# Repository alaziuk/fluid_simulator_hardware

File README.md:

# Fluid Simulator Pendant Hardware

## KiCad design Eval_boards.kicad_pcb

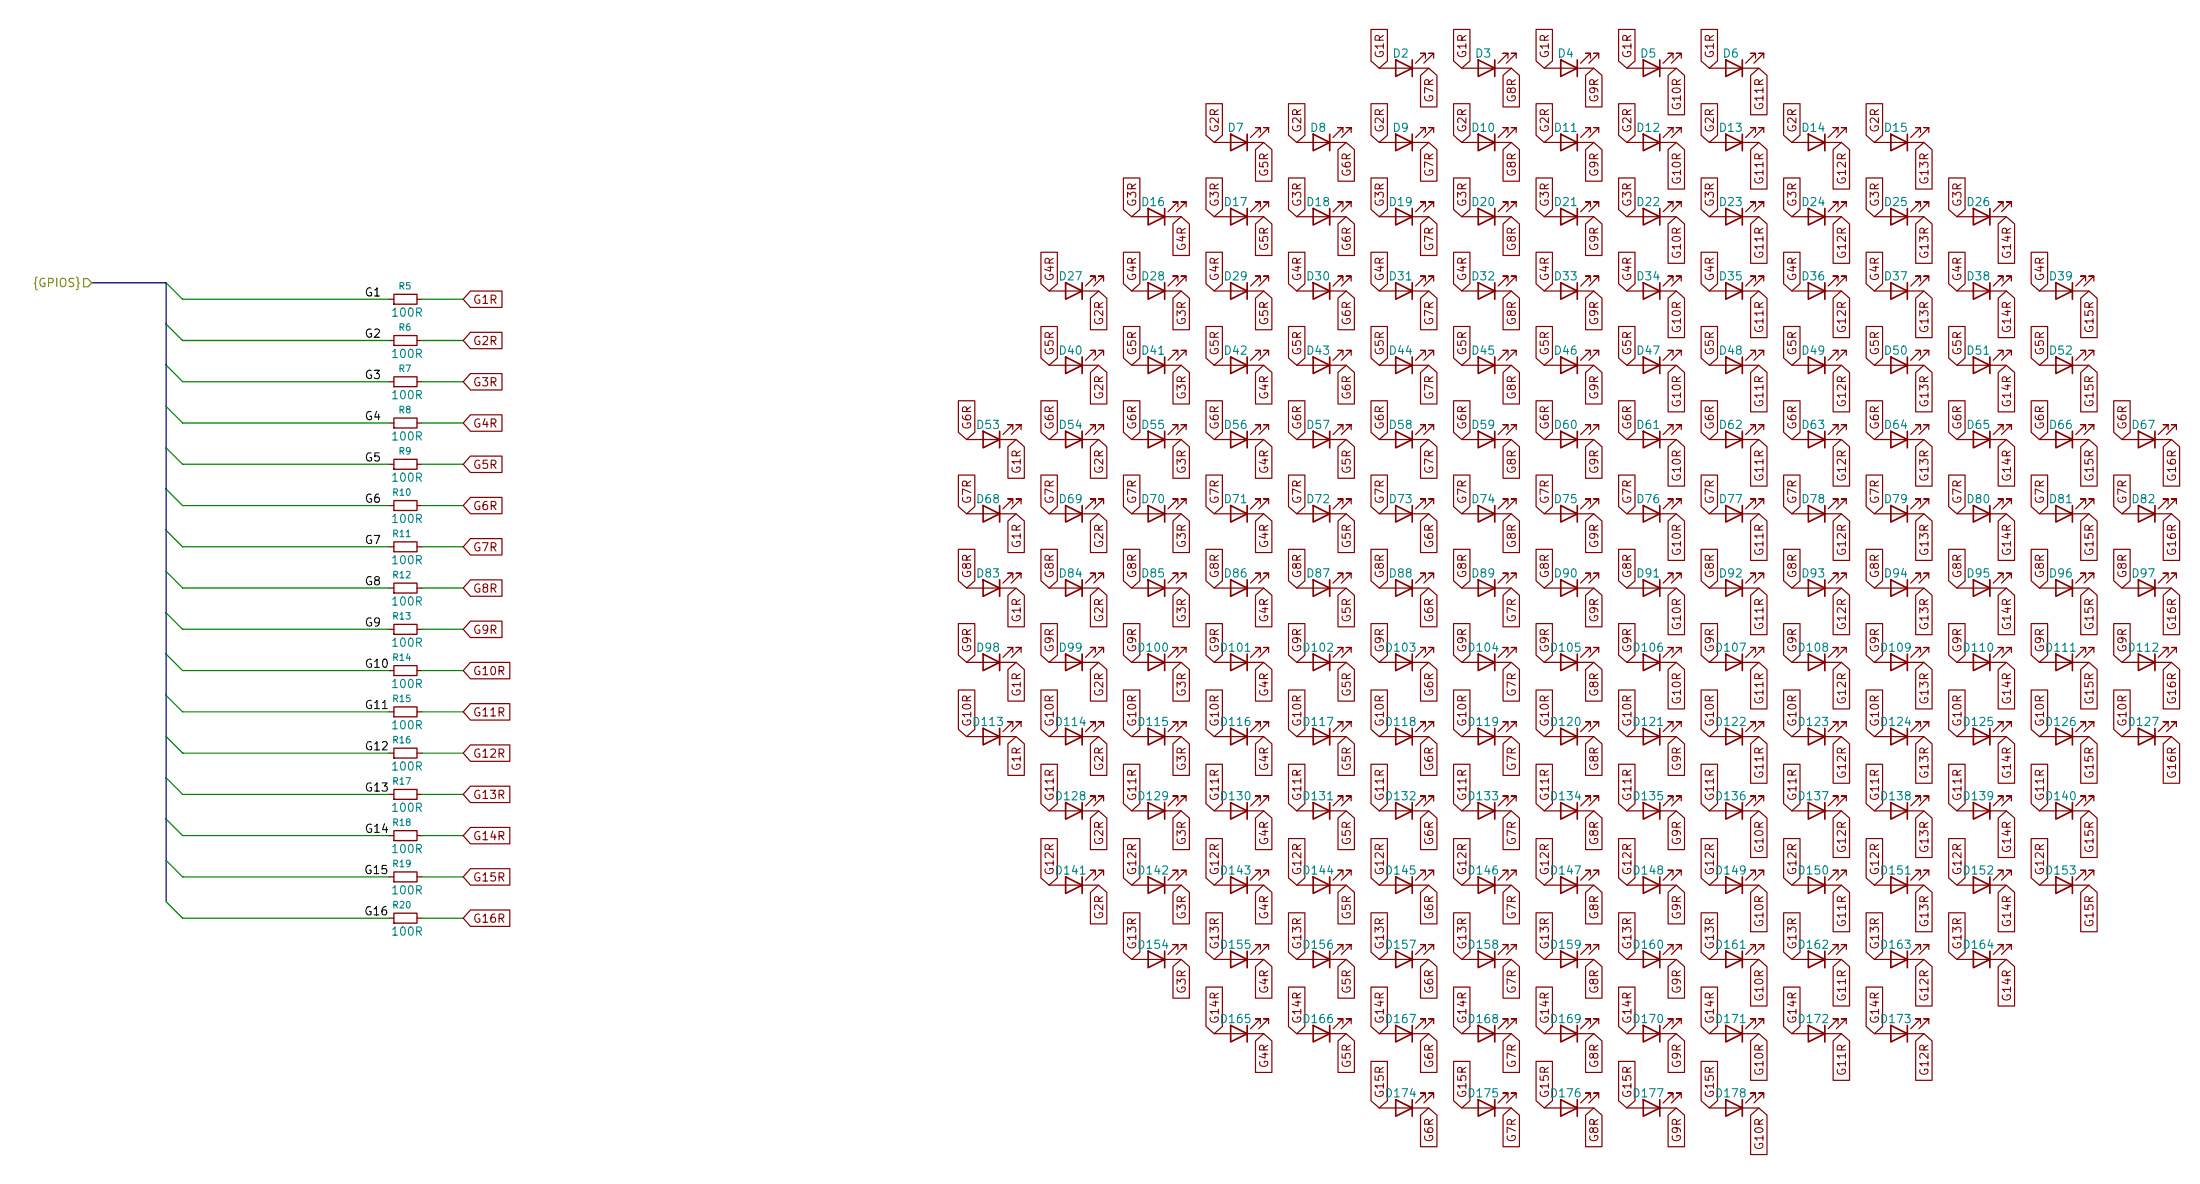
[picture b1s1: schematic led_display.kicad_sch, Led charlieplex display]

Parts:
D2, D3, D4, D5, D6, D7, D8, D9, D10, D11, D12, D13, D14, D15, D16, D17, D18, D19, D20, D21, D22, D23, D24, D25, D26, D27, D28, D29, D30, D31, D32, D33, D34, D35, D36, D37, D38, D39, D40, D41, D42, D43, D44, D45, D46, D47, D48, D49, D50, D51, D52, D53, D54, D55, D56, D57, D58, D59, D60, D61, D62, D63, D64, D65, D66, D67, D68, D69, D70, D71, D72, D73, D74, D75, D76, D77, D78, D79, D80, D81, D82, D83, D84, D85, D86, D87, D88, D89, D90, D91, D92, D93, D94, D95, D96, D97, D98, D99, D100, D101, D102, D103, D104, D105, D106, D107, D108, D109, D110, D111, D112, D113, D114, D115, D116, D117, D118, D119, D120, D121, D122, D123, D124, D125, D126, D127, D128, D129, D130, D131, D132, D133, D134, D135, D136, D137, D138, D139, D140, D141, D142, D143, D144, D145, D146, D147, D148, D149, D150, D151, D152, D153, D154, D155, D156, D157, D158, D159, D160, D161, D162, D163, D164, D165, D166, D167, D168, D169, D170, D171, D172, D173, D174, D175, D176, D177, D178: blue led; D_0603_1608Metric
R5, R6, R7, R8, R9, R10, R11, R12, R13, R14, R15, R16, R17, R18, R19, R20: 100R; R_0603_1608Metric

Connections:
/LED_DISPLAY/G1: R5.1; also elsewhere on the board
/LED_DISPLAY/G2: R6.1; also elsewhere on the board
/LED_DISPLAY/G3: R7.1; also elsewhere on the board
/LED_DISPLAY/G4: R8.1; also elsewhere on the board
/LED_DISPLAY/G5: R9.1; also elsewhere on the board
/LED_DISPLAY/G6: R10.1; also elsewhere on the board
/LED_DISPLAY/G7: R11.1; also elsewhere on the board
/LED_DISPLAY/G8: R12.1; also elsewhere on the board
/LED_DISPLAY/G9: R13.1; also elsewhere on the board
/LED_DISPLAY/G10: R14.1; also elsewhere on the board
/LED_DISPLAY/G11: R15.1; also elsewhere on the board
/LED_DISPLAY/G12: R16.1; also elsewhere on the board
/LED_DISPLAY/G13: R17.1; also elsewhere on the board
/LED_DISPLAY/G14: R18.1; also elsewhere on the board
/LED_DISPLAY/G15: R19.1; also elsewhere on the board
/LED_DISPLAY/G16: R20.1; also elsewhere on the board
G1R: D2.2 (A), D3.2 (A), D4.2 (A), D5.2 (A), D6.2 (A), D53.1 (K), D68.1 (K), D83.1 (K), D98.1 (K), D113.1 (K), R5.2
G2R: D7.2 (A), D8.2 (A), D9.2 (A), D10.2 (A), D11.2 (A), D12.2 (A), D13.2 (A), D14.2 (A), D15.2 (A), D27.1 (K), D40.1 (K), D54.1 (K), D69.1 (K), D84.1 (K), D99.1 (K), D114.1 (K), D128.1 (K), D141.1 (K), R6.2
G3R: D16.2 (A), D17.2 (A), D18.2 (A), D19.2 (A), D20.2 (A), D21.2 (A), D22.2 (A), D23.2 (A), D24.2 (A), D25.2 (A), D26.2 (A), D28.1 (K), D41.1 (K), D55.1 (K), D70.1 (K), D85.1 (K), D100.1 (K), D115.1 (K), D129.1 (K), D142.1 (K), D154.1 (K), R7.2
G4R: D16.1 (K), D27.2 (A), D28.2 (A), D29.2 (A), D30.2 (A), D31.2 (A), D32.2 (A), D33.2 (A), D34.2 (A), D35.2 (A), D36.2 (A), D37.2 (A), D38.2 (A), D39.2 (A), D42.1 (K), D56.1 (K), D71.1 (K), D86.1 (K), D101.1 (K), D116.1 (K), D130.1 (K), D143.1 (K), D155.1 (K), D165.1 (K), R8.2
G5R: D7.1 (K), D17.1 (K), D29.1 (K), D40.2 (A), D41.2 (A), D42.2 (A), D43.2 (A), D44.2 (A), D45.2 (A), D46.2 (A), D47.2 (A), D48.2 (A), D49.2 (A), D50.2 (A), D51.2 (A), D52.2 (A), D57.1 (K), D72.1 (K), D87.1 (K), D102.1 (K), D117.1 (K), D131.1 (K), D144.1 (K), D156.1 (K), D166.1 (K), R9.2
G6R: D8.1 (K), D18.1 (K), D30.1 (K), D43.1 (K), D53.2 (A), D54.2 (A), D55.2 (A), D56.2 (A), D57.2 (A), D58.2 (A), D59.2 (A), D60.2 (A), D61.2 (A), D62.2 (A), D63.2 (A), D64.2 (A), D65.2 (A), D66.2 (A), D67.2 (A), D73.1 (K), D88.1 (K), D103.1 (K), D118.1 (K), D132.1 (K), D145.1 (K), D157.1 (K), D167.1 (K), D174.1 (K), R10.2
G7R: D2.1 (K), D9.1 (K), D19.1 (K), D31.1 (K), D44.1 (K), D58.1 (K), D68.2 (A), D69.2 (A), D70.2 (A), D71.2 (A), D72.2 (A), D73.2 (A), D74.2 (A), D75.2 (A), D76.2 (A), D77.2 (A), D78.2 (A), D79.2 (A), D80.2 (A), D81.2 (A), D82.2 (A), D89.1 (K), D104.1 (K), D119.1 (K), D133.1 (K), D146.1 (K), D158.1 (K), D168.1 (K), D175.1 (K), R11.2
G8R: D3.1 (K), D10.1 (K), D20.1 (K), D32.1 (K), D45.1 (K), D59.1 (K), D74.1 (K), D83.2 (A), D84.2 (A), D85.2 (A), D86.2 (A), D87.2 (A), D88.2 (A), D89.2 (A), D90.2 (A), D91.2 (A), D92.2 (A), D93.2 (A), D94.2 (A), D95.2 (A), D96.2 (A), D97.2 (A), D105.1 (K), D120.1 (K), D134.1 (K), D147.1 (K), D159.1 (K), D169.1 (K), D176.1 (K), R12.2
G9R: D4.1 (K), D11.1 (K), D21.1 (K), D33.1 (K), D46.1 (K), D60.1 (K), D75.1 (K), D90.1 (K), D98.2 (A), D99.2 (A), D100.2 (A), D101.2 (A), D102.2 (A), D103.2 (A), D104.2 (A), D105.2 (A), D106.2 (A), D107.2 (A), D108.2 (A), D109.2 (A), D110.2 (A), D111.2 (A), D112.2 (A), D121.1 (K), D135.1 (K), D148.1 (K), D160.1 (K), D170.1 (K), D177.1 (K), R13.2
G10R: D5.1 (K), D12.1 (K), D22.1 (K), D34.1 (K), D47.1 (K), D61.1 (K), D76.1 (K), D91.1 (K), D106.1 (K), D113.2 (A), D114.2 (A), D115.2 (A), D116.2 (A), D117.2 (A), D118.2 (A), D119.2 (A), D120.2 (A), D121.2 (A), D122.2 (A), D123.2 (A), D124.2 (A), D125.2 (A), D126.2 (A), D127.2 (A), D136.1 (K), D149.1 (K), D161.1 (K), D171.1 (K), D178.1 (K), R14.2
G11R: D6.1 (K), D13.1 (K), D23.1 (K), D35.1 (K), D48.1 (K), D62.1 (K), D77.1 (K), D92.1 (K), D107.1 (K), D122.1 (K), D128.2 (A), D129.2 (A), D130.2 (A), D131.2 (A), D132.2 (A), D133.2 (A), D134.2 (A), D135.2 (A), D136.2 (A), D137.2 (A), D138.2 (A), D139.2 (A), D140.2 (A), D150.1 (K), D162.1 (K), D172.1 (K), R15.2
G12R: D14.1 (K), D24.1 (K), D36.1 (K), D49.1 (K), D63.1 (K), D78.1 (K), D93.1 (K), D108.1 (K), D123.1 (K), D137.1 (K), D141.2 (A), D142.2 (A), D143.2 (A), D144.2 (A), D145.2 (A), D146.2 (A), D147.2 (A), D148.2 (A), D149.2 (A), D150.2 (A), D151.2 (A), D152.2 (A), D153.2 (A), D163.1 (K), D173.1 (K), R16.2
G13R: D15.1 (K), D25.1 (K), D37.1 (K), D50.1 (K), D64.1 (K), D79.1 (K), D94.1 (K), D109.1 (K), D124.1 (K), D138.1 (K), D151.1 (K), D154.2 (A), D155.2 (A), D156.2 (A), D157.2 (A), D158.2 (A), D159.2 (A), D160.2 (A), D161.2 (A), D162.2 (A), D163.2 (A), D164.2 (A), R17.2
G14R: D26.1 (K), D38.1 (K), D51.1 (K), D65.1 (K), D80.1 (K), D95.1 (K), D110.1 (K), D125.1 (K), D139.1 (K), D152.1 (K), D164.1 (K), D165.2 (A), D166.2 (A), D167.2 (A), D168.2 (A), D169.2 (A), D170.2 (A), D171.2 (A), D172.2 (A), D173.2 (A), R18.2
G15R: D39.1 (K), D52.1 (K), D66.1 (K), D81.1 (K), D96.1 (K), D111.1 (K), D126.1 (K), D140.1 (K), D153.1 (K), D174.2 (A), D175.2 (A), D176.2 (A), D177.2 (A), D178.2 (A), R19.2
G16R: D67.1 (K), D82.1 (K), D97.1 (K), D112.1 (K), D127.1 (K), R20.2

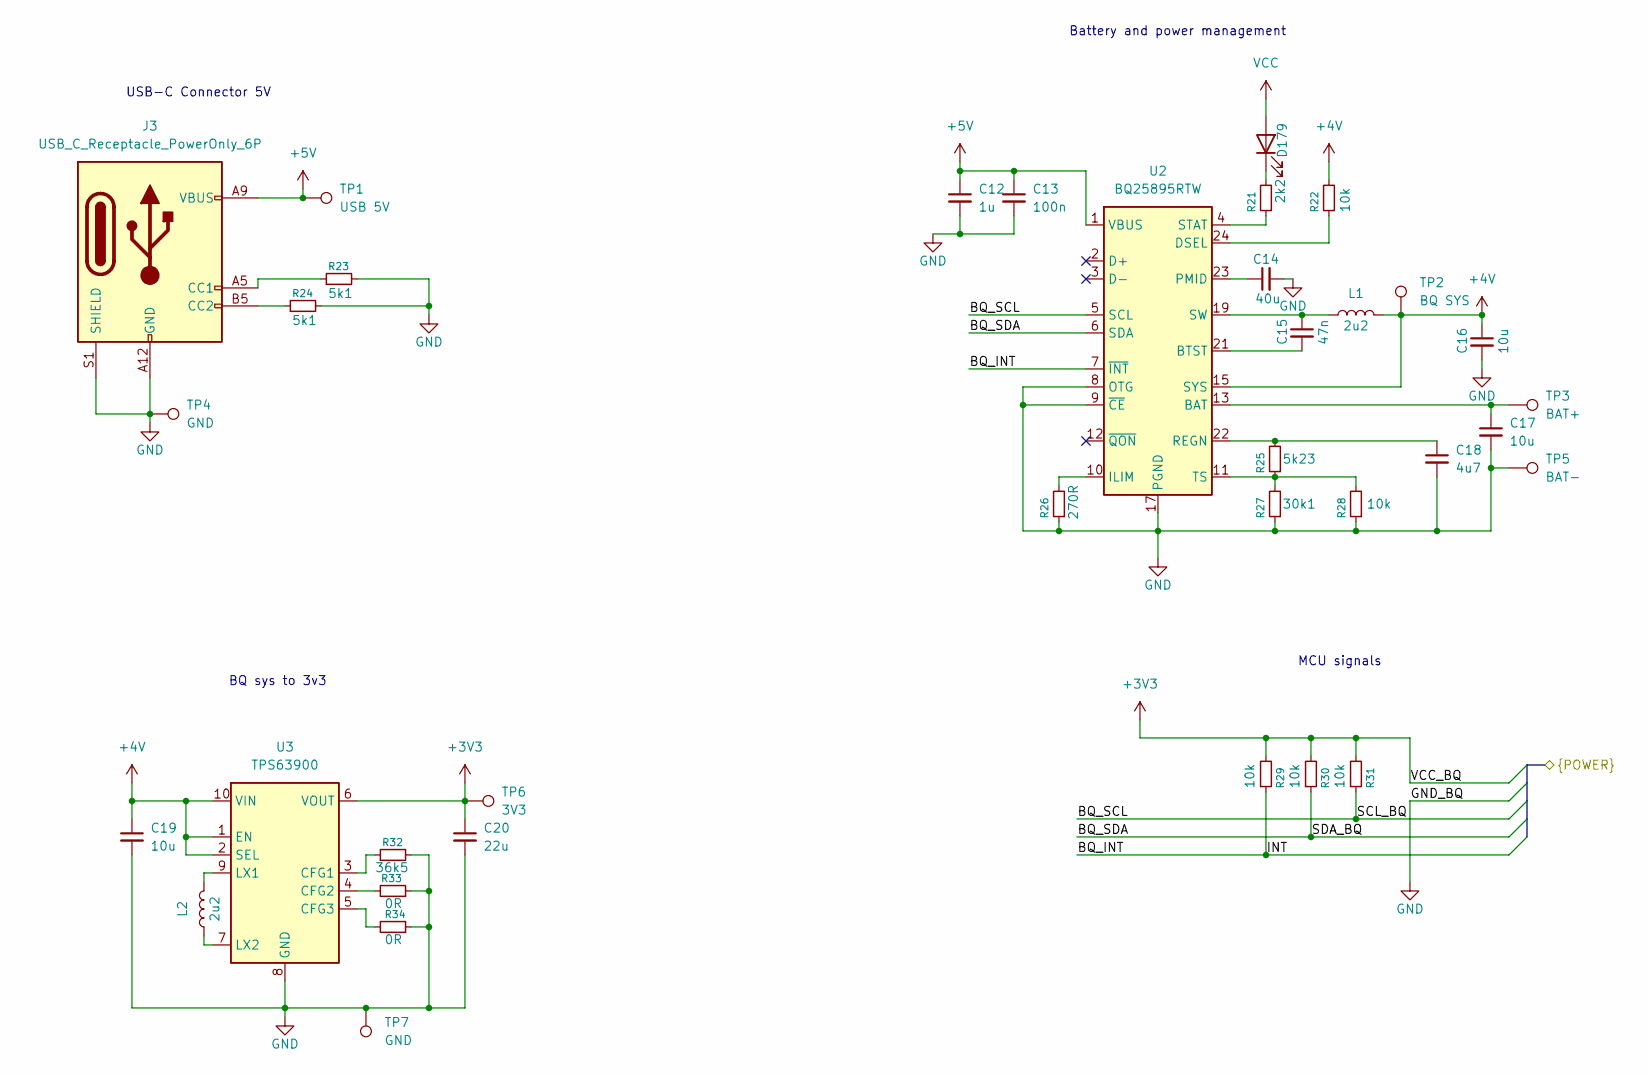
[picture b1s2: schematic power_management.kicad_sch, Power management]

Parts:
C12: 1u; C_0603_1608Metric
C13: 100n; C_0603_1608Metric
C14: 40u; C_0603_1608Metric
C15: 47n; C_0603_1608Metric
C16, C17, C19: 10u; C_0603_1608Metric
C18: 4u7; C_0603_1608Metric
C20: 22u; C_0603_1608Metric
D179: blue led; D_0603_1608Metric
J3: USB_C_Receptacle_PowerOnly_6P; USB_C_Receptacle_GCT_USB4135-GF-A_6P_TopMnt_Horizontal
L1, L2: 2u2; L_0603_1608Metric
R21: 2k2; R_0603_1608Metric
R22, R28, R29, R30, R31: 10k; R_0603_1608Metric
R23, R24: 5k1; R_0603_1608Metric
R25: 5k23; R_0603_1608Metric
R26: 270R; R_0603_1608Metric
R27: 30k1; R_0603_1608Metric
R32: 36k5; R_0603_1608Metric
R33, R34: 0R; R_0603_1608Metric
TP1: USB 5V; TestPoint_Pad_D1.0mm
TP2: BQ SYS; TestPoint_Pad_D1.0mm
TP3: BAT+; TestPoint_Pad_D2.5mm
TP4, TP7: GND; TestPoint_Pad_D1.0mm
TP5: BAT-; TestPoint_Pad_D2.5mm
TP6: 3V3; TestPoint_Pad_D1.0mm
U2: BQ25895RTW; Texas_RTW_WQFN-24-1EP_4x4mm_P0.5mm_EP2.7x2.7mm_ThermalVias
U3: TPS63900; WSON-10-1EP_2.5x2.5mm_P0.5mm_EP1.2x2mm_ThermalVias

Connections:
+3V3: C20.1, R29.2, R30.2, R31.2, TP6.1, U3.6 (VOUT); also elsewhere on the board
+4V: C16.1, C19.1, L1.2, R22.2, TP2.1, U2.15 (SYS), U2.16 (SYS), U3.1 (EN), U3.2 (SEL), U3.10 (VIN); also elsewhere on the board
+5V: C12.1, C13.1, J3.A9 (VBUS), J3.B9 (VBUS), TP1.1, U2.1 (VBUS); also elsewhere on the board
/ACCELEROMETER/SCL_A: R31.1, U2.5 (SCL); also elsewhere on the board
/ACCELEROMETER/SDA_A: R30.1, U2.6 (SDA); also elsewhere on the board
/MCU/INT: R29.1, U2.7 (~INT); also elsewhere on the board
GND: C12.2, C13.2, C14.2, C16.2, C17.2, C18.2, C19.2, C20.2, J3.A12 (GND), J3.B12 (GND), J3.S1 (SHIELD), R23.2, R24.2, R26.1, R27.1, R28.1, R32.2, R33.1, R34.1, TP4.1, TP5.1, TP7.1, U2.8 (OTG), U2.9 (~CE), U2.17 (PGND), U2.18 (PGND), U2.25 (PGND), U3.8 (GND), U3.11 (GND); also elsewhere on the board
unnamed: C15.1, L1.1, U2.19 (SW), U2.20 (SW)
unnamed 54: C17.1, TP3.1, U2.13 (BAT), U2.14 (BAT); also elsewhere on the board
unnamed: D179.1 (K), R21.2
unnamed: J3.A5 (CC1), R23.1
unnamed: J3.B5 (CC2), R24.1
unnamed: C15.2, U2.21 (BTST)
unnamed: R22.1, U2.24 (DSEL)
unnamed: R26.2, U2.10 (ILIM)
unnamed: C14.1, U2.23 (PMID)
unnamed: C18.1, R25.2, U2.22 (REGN)
unnamed: R21.1, U2.4 (STAT)
unnamed: R25.1, R27.2, R28.2, U2.11 (TS)
unnamed: R32.1, U3.3 (CFG1)
unnamed: R33.2, U3.4 (CFG2)
unnamed: R34.2, U3.5 (CFG3)
unnamed: L2.1, U3.9 (LX1)
unnamed: L2.2, U3.7 (LX2)
VCC: D179.2 (A)

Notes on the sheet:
BQ sys to 3v3
MCU signals
Battery and power management
USB-C Connector 5V

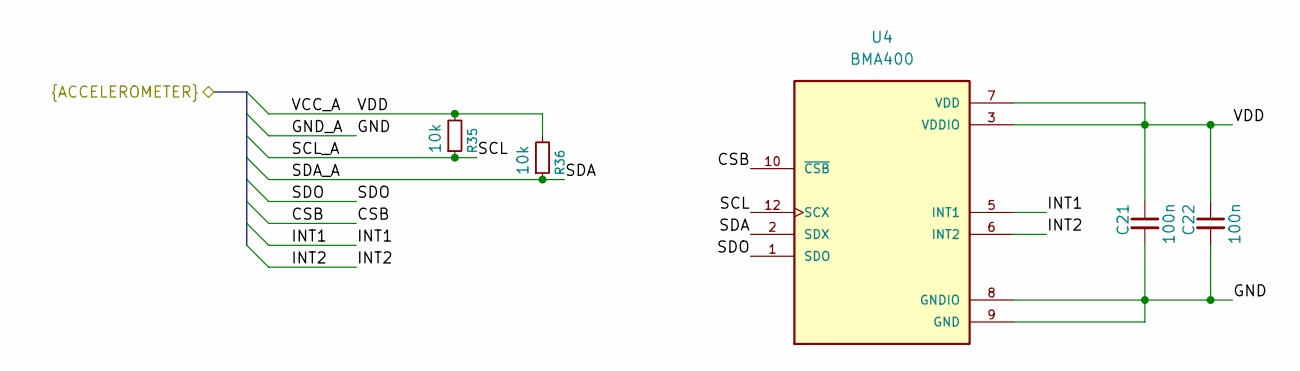
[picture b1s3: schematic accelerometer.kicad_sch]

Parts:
C21, C22: 100n; C_0603_1608Metric
R35, R36: 10k; R_0603_1608Metric
U4: BMA400; XDCR_BMA400

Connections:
+3V3: C21.1, C22.1, R35.2, R36.2, U4.3 (VDDIO), U4.7 (VDD), U4.10 (~CSB); also elsewhere on the board
/ACCELEROMETER/INT1: U4.5 (INT1); also elsewhere on the board
/ACCELEROMETER/INT2: U4.6 (INT2); also elsewhere on the board
/ACCELEROMETER/SCL_A: R35.1, U4.12 (SCX); also elsewhere on the board
/ACCELEROMETER/SDA_A: R36.1, U4.2 (SDX); also elsewhere on the board
/ACCELEROMETER/SDO: U4.1 (SDO); also elsewhere on the board
GND: C21.2, C22.2, U4.8 (GNDIO), U4.9 (GND); also elsewhere on the board

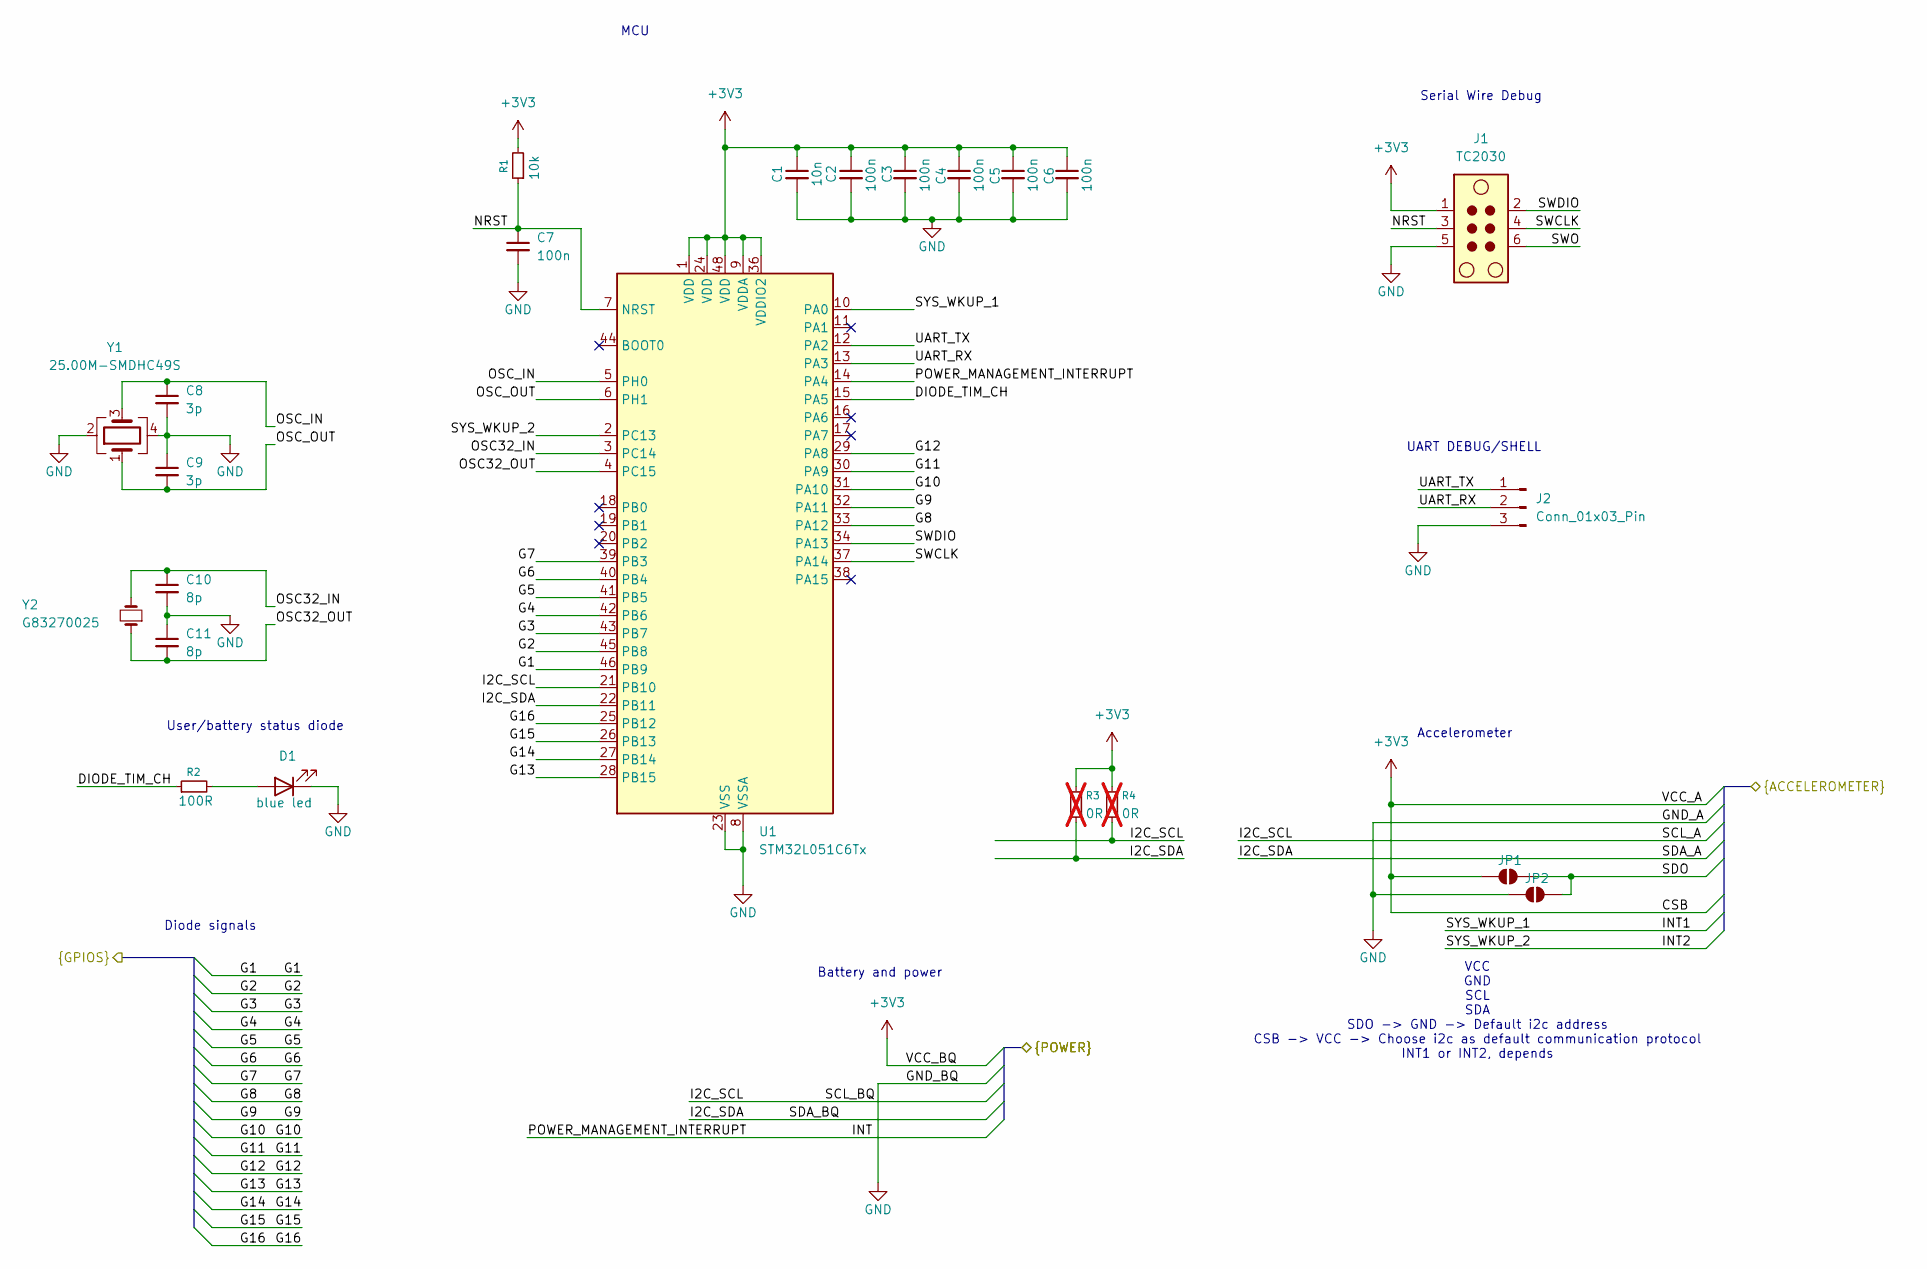
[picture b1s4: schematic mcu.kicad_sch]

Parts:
C1: 10n; C_0603_1608Metric
C2, C3, C4, C5, C6, C7: 100n; C_0603_1608Metric
C8, C9: 3p; C_0603_1608Metric
C10, C11: 8p; C_0603_1608Metric
D1: blue led; D_0603_1608Metric
J1: TC2030; Tag-Connect_TC2030-IDC-NL_2x03_P1.27mm_Vertical
J2: Conn_01x03_Pin; JST_GH_BM03B-GHS-TBT_1x03-1MP_P1.25mm_Vertical
JP1, JP2: SolderJumper_2_Open; SolderJumper-2_P1.3mm_Open_TrianglePad1.0x1.5mm
R1: 10k; R_0603_1608Metric
R2: 100R; R_0603_1608Metric
R3, R4: 0R; R_0603_1608Metric; not fitted
U1: STM32L051C6Tx; LQFP-48_7x7mm_P0.5mm
Y1: 25.00M-SMDHC49S; Crystal_SMD_3225-4Pin_3.2x2.5mm
Y2: G83270025; Crystal_SMD_3215-2Pin_3.2x1.5mm

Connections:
+3V3: C1.1, C2.1, C3.1, C4.1, C5.1, C6.1, J1.1, JP1.1 (A), R1.2, R3.1, R4.1, U1.1 (VDD), U1.9 (VDDA), U1.24 (VDD), U1.36 (VDDIO2), U1.48 (VDD); also elsewhere on the board
/ACCELEROMETER/INT1: U1.10 (PA0); also elsewhere on the board
/ACCELEROMETER/INT2: U1.2 (PC13); also elsewhere on the board
/ACCELEROMETER/SCL_A: R4.2, U1.21 (PB10); also elsewhere on the board
/ACCELEROMETER/SDA_A: R3.2, U1.22 (PB11); also elsewhere on the board
/ACCELEROMETER/SDO: JP1.2 (B), JP2.2 (B); also elsewhere on the board
/LED_DISPLAY/G1: U1.46 (PB9); also elsewhere on the board
/LED_DISPLAY/G2: U1.45 (PB8); also elsewhere on the board
/LED_DISPLAY/G3: U1.43 (PB7); also elsewhere on the board
/LED_DISPLAY/G4: U1.42 (PB6); also elsewhere on the board
/LED_DISPLAY/G5: U1.41 (PB5); also elsewhere on the board
/LED_DISPLAY/G6: U1.40 (PB4); also elsewhere on the board
/LED_DISPLAY/G7: U1.39 (PB3); also elsewhere on the board
/LED_DISPLAY/G8: U1.33 (PA12); also elsewhere on the board
/LED_DISPLAY/G9: U1.32 (PA11); also elsewhere on the board
/LED_DISPLAY/G10: U1.31 (PA10); also elsewhere on the board
/LED_DISPLAY/G11: U1.30 (PA9); also elsewhere on the board
/LED_DISPLAY/G12: U1.29 (PA8); also elsewhere on the board
/LED_DISPLAY/G13: U1.28 (PB15); also elsewhere on the board
/LED_DISPLAY/G14: U1.27 (PB14); also elsewhere on the board
/LED_DISPLAY/G15: U1.26 (PB13); also elsewhere on the board
/LED_DISPLAY/G16: U1.25 (PB12); also elsewhere on the board
/MCU/DIODE_TIM_CH: R2.1, U1.15 (PA5)
/MCU/INT: U1.14 (PA4); also elsewhere on the board
/MCU/NRST: C7.1, J1.3, R1.1, U1.7 (NRST)
/MCU/OSC32_IN: C10.1, U1.3 (PC14), Y2.2
/MCU/OSC32_OUT: C11.2, U1.4 (PC15), Y2.1
/MCU/OSC_IN: C8.1, U1.5 (PH0), Y1.3
/MCU/OSC_OUT: C9.2, U1.6 (PH1), Y1.1
/MCU/SWCLK: J1.4, U1.37 (PA14)
/MCU/SWDIO: J1.2, U1.34 (PA13)
/MCU/SWO: J1.6
/MCU/UART_RX: J2.2, U1.13 (PA3)
/MCU/UART_TX: J2.1, U1.12 (PA2)
GND: C1.2, C2.2, C3.2, C4.2, C5.2, C6.2, C7.2, C8.2, C9.1, C10.2, C11.1, D1.1 (K), J1.5, J2.3, JP2.1 (A), U1.8 (VSSA), U1.23 (VSS), U1.35 (VSS), U1.47 (VSS), Y1.2, Y1.4; also elsewhere on the board
unnamed: D1.2 (A), R2.2

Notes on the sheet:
User/battery status diode
UART DEBUG/SHELL
MCU
Diode signals
VCC GND SCL SDA SDO -> GND -> Default i2c address CSB -> VCC -> Choose i2c as default communication protocol INT1 or INT2, depends
Serial Wire Debug
Accelerometer
Battery and power

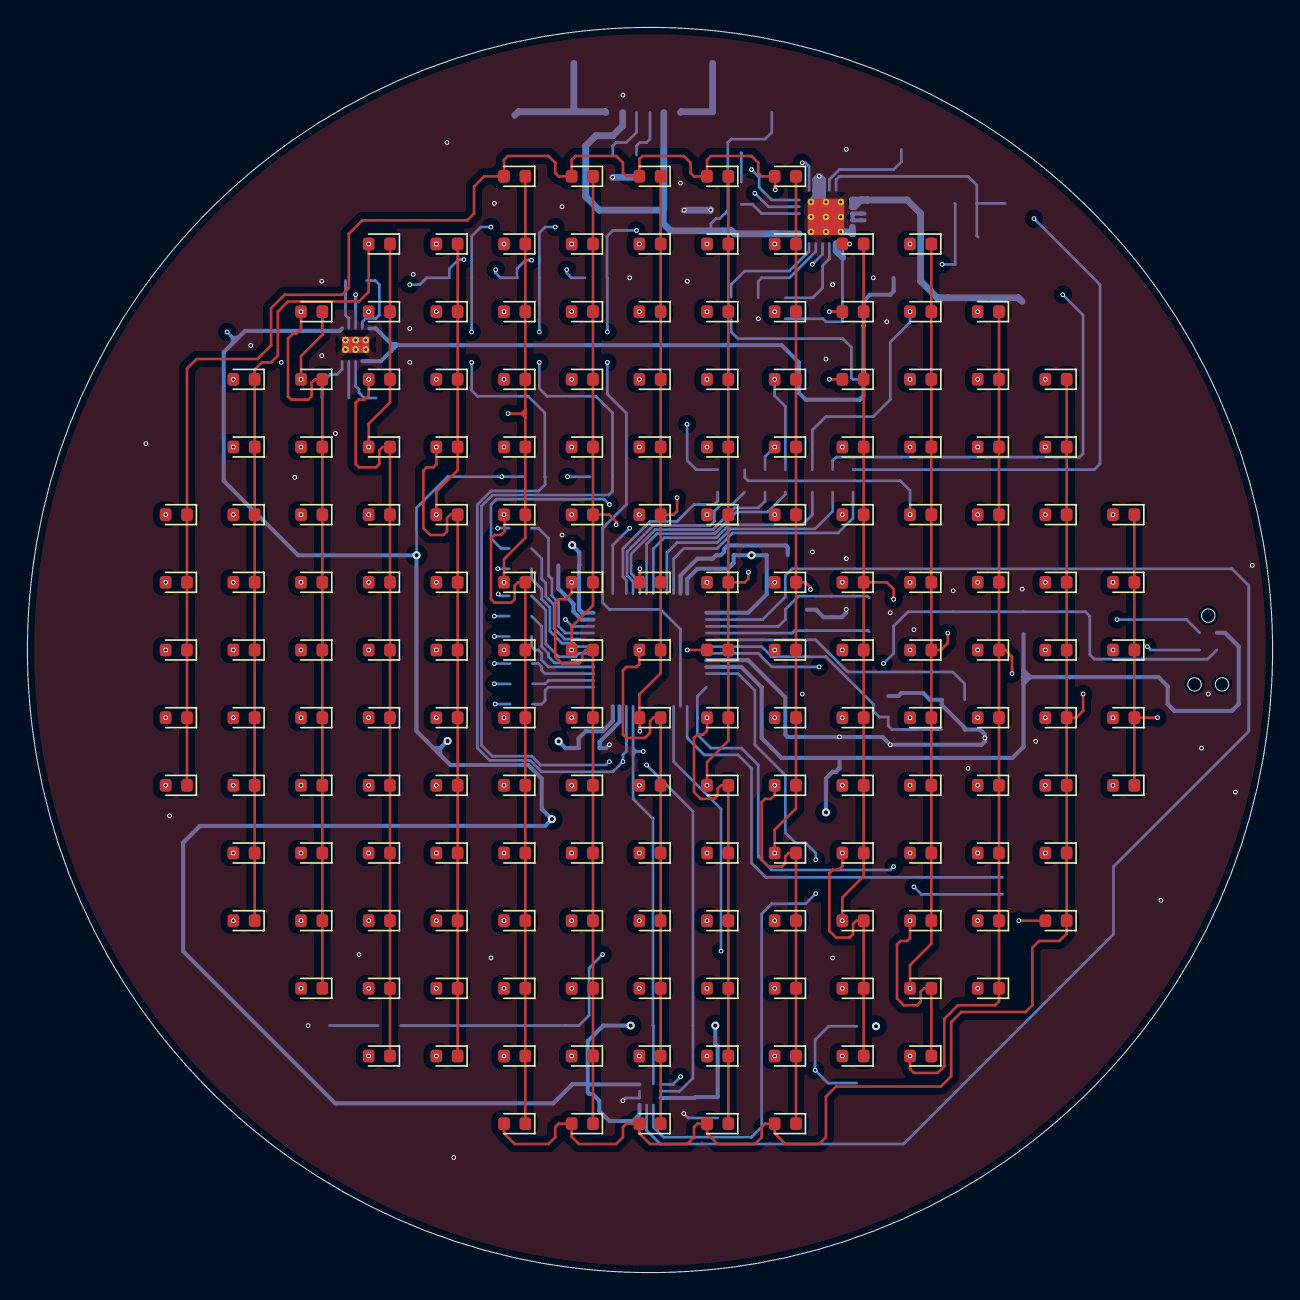
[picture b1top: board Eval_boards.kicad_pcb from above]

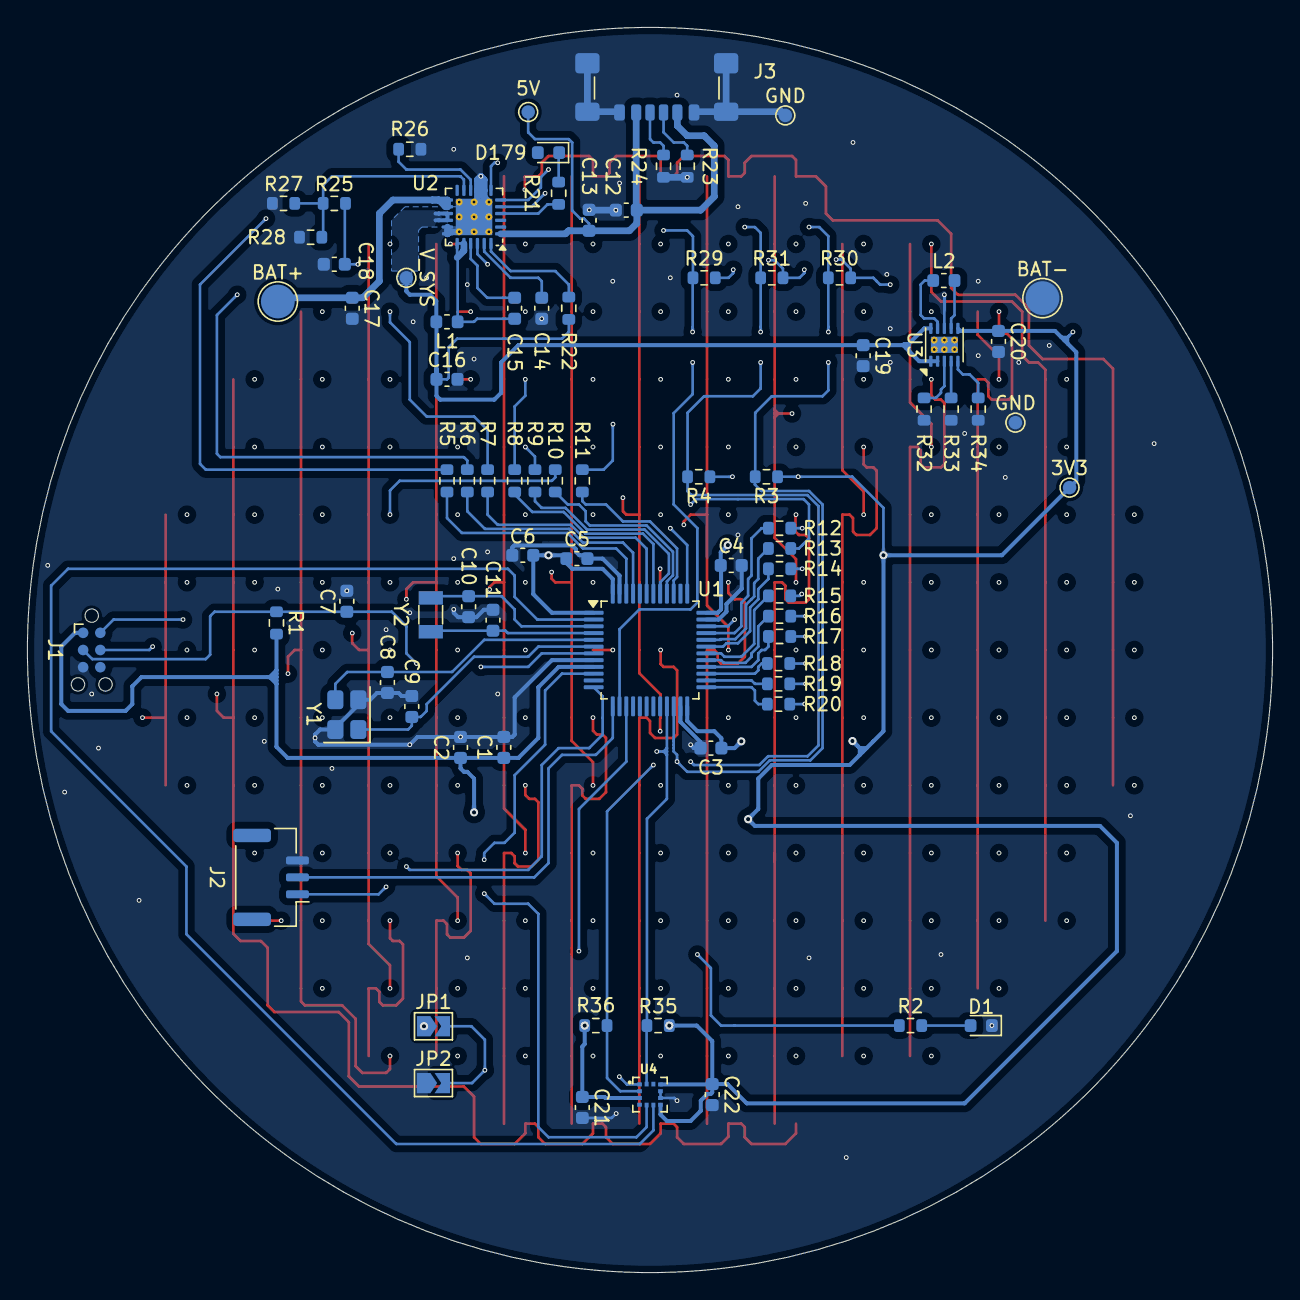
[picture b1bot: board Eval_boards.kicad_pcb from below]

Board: 4 copper layers, 92.0 x 92.0 mm, 257 parts (80 on the bottom side), 70 nets.

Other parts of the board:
3V3: 3V3; TestPoint_Pad_D1.0mm
5V: USB 5V; TestPoint_Pad_D1.0mm
BAT+: BAT+; TestPoint_Pad_D2.5mm
BAT-: BAT-; TestPoint_Pad_D2.5mm
GND: GND; TestPoint_Pad_D1.0mm
GND#2: GND; TestPoint_Pad_D1.0mm
V_SYS: BQ SYS; TestPoint_Pad_D1.0mm

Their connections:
+3V3: 3V3.1; also elsewhere on the board
+4V: V_SYS.1; also elsewhere on the board
+5V: 5V.1; also elsewhere on the board
GND: BAT-.1, GND.1, GND#2.1; also elsewhere on the board
unnamed 54: BAT+.1; also elsewhere on the board

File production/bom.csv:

Designator,Footprint,Quantity,Value,LCSC Part #
3V3,TestPoint_Pad_D1.0mm,1,3V3,
5V,TestPoint_Pad_D1.0mm,1,USB 5V,
BAT+,TestPoint_Pad_D2.5mm,1,BAT+,
BAT-,TestPoint_Pad_D2.5mm,1,BAT-,
C1,0603,1,10n,
"C10, C11",0603,2,8p,
C12,0603,1,1u,
"C13, C2, C21, C22, C3, C4, C5, C6, C7",0603,9,100n,
C14,0603,1,40u,
C15,0603,1,47n,
"C16, C17, C19",0603,3,10u,
C18,0603,1,4u7,
C20,0603,1,22u,
"C8, C9",0603,2,3p,
"D1, D10, D100, D101, D102, D103, D104, D105, D106, D107, D108, D109, D11, D110, D111, D112, D113, D114, D115, D116, D117, D118, D119, D12, D120, D121, D122, D123, D124, D125, D126, D127, D128, D129, D13, D130, D131, D132, D133, D134, D135, D136, D137, D138, D139, D14, D140, D141, D142, D143, D144, D145, D146, D147, D148, D149, D15, D150, D151, D152, D153, D154, D155, D156, D157, D158, D159, D16, D160, D161, D162, D163, D164, D165, D166, D167, D168, D169, D17, D170, D171, D172, D173, D174, D175, D176, D177, D178, D179, D18, D19, D2, D20, D21, D22, D23, D24, D25, D26, D27, D28, D29, D3, D30, D31, D32, D33, D34, D35, D36, D37, D38, D39, D4, D40, D41, D42, D43, D44, D45, D46, D47, D48, D49, D5, D50, D51, D52, D53, D54, D55, D56, D57, D58, D59, D6, D60, D61, D62, D63, D64, D65, D66, D67, D68, D69, D7, D70, D71, D72, D73, D74, D75, D76, D77, D78, D79, D8, D80, D81, D82, D83, D84, D85, D86, D87, D88, D89, D9, D90, D91, D92, D93, D94, D95, D96, D97, D98, D99",0603,179,blue led,
"GND_2, GND",TestPoint_Pad_D1.0mm,2,GND,
J2,JST_GH_BM03B-GHS-TBT_1x03-1MP_P1.25mm_Vertical,1,Conn_01x03_Pin,
J3,USB_C_Receptacle_GCT_USB4135-GF-A_6P_TopMnt_Horizontal,1,USB_C_Receptacle_PowerOnly_6P,
"L1, L2",0603,2,2u2,
"R1, R22, R28, R29, R30, R31, R35, R36",0603,8,10k,
"R10, R11, R12, R13, R14, R15, R16, R17, R18, R19, R2, R20, R5, R6, R7, R8, R9",0603,17,100R,
R21,0603,1,2k2,
"R23, R24",0603,2,5k1,
R25,0603,1,5k23,
R26,0603,1,270R,
R27,0603,1,30k1,
"R3, R33, R34, R4",0603,4,0R,
R32,0603,1,36k5,
U1,LQFP-48_7x7mm_P0.5mm,1,STM32L051C6Tx,
U2,Texas_RTW_WQFN-24-1EP_4x4mm_P0.5mm_EP2.7x2.7mm_ThermalVias,1,BQ25895RTW,
U3,WSON-10-1EP_2.5x2.5mm_P0.5mm_EP1.2x2mm_ThermalVias,1,TPS63900,
U4,XDCR_BMA400,1,BMA400,
V_SYS,TestPoint_Pad_D1.0mm,1,BQ SYS,
Y1,Crystal_SMD_3225-4Pin_3.2x2.5mm,1,25.00M-SMDHC49S,
Y2,Crystal_SMD_3215-2Pin_3.2x1.5mm,1,G83270025,

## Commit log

2025-09-23 Change of concept - one board, not multiple
2025-09-26 Early pcb project
2025-10-18 Finished pcb project
2025-12-21 Add new mcu and better leds layout
2025-12-21 Crystal resonator change
